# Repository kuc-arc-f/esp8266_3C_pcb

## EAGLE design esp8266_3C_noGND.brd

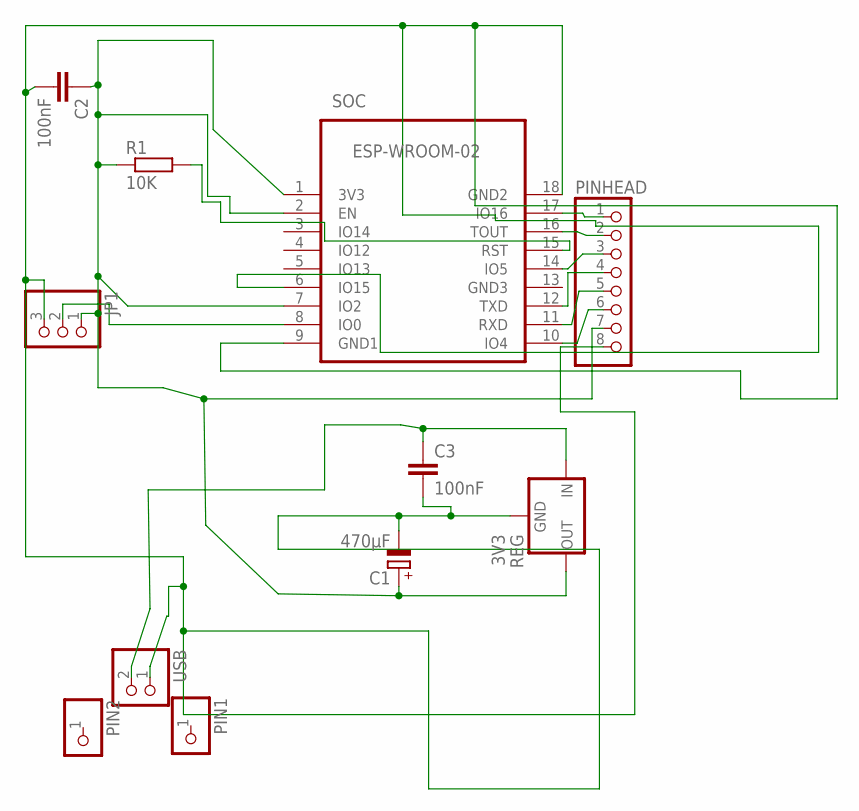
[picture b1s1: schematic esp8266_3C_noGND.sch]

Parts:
C1: 470μF; E2,5-7
C2, C3: 100nF; C0603
JP1: PINHD-1X3; 1X03
PIN1, PIN2: PINHD-1X1; 1X01
PINHEAD: PINHD-1X8; 1X08
R1: 10K; R0603
REG: 3V3; 78XXS
SOC: ESP-WROOM-02; FRONT-FACE-CP2
USB: PINHD-1X2; 1X02

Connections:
unnamed: JP1.2, SOC.8 (IO0)
unnamed: C3.1, REG.IN, USB.2
unnamed: PINHEAD.1, SOC.17 (IO16)
unnamed: PINHEAD.2, SOC.16 (TOUT)
unnamed: PINHEAD.3, SOC.14 (IO5)
unnamed: PINHEAD.4, SOC.12 (TXD)
unnamed: PINHEAD.5, SOC.11 (RXD)
unnamed: PINHEAD.6, SOC.10 (IO4)
unnamed: C1.+, C2.1, JP1.1, PINHEAD.7, R1.1, REG.OUT, SOC.1 (3V3), SOC.2 (EN), SOC.7 (IO2)
unnamed: R1.2, SOC.15 (RST)
USB: C1.-, C2.2, C3.2, JP1.3, PINHEAD.8, REG.GND, SOC.6 (IO15), SOC.9 (GND1), SOC.18 (GND2), USB.1

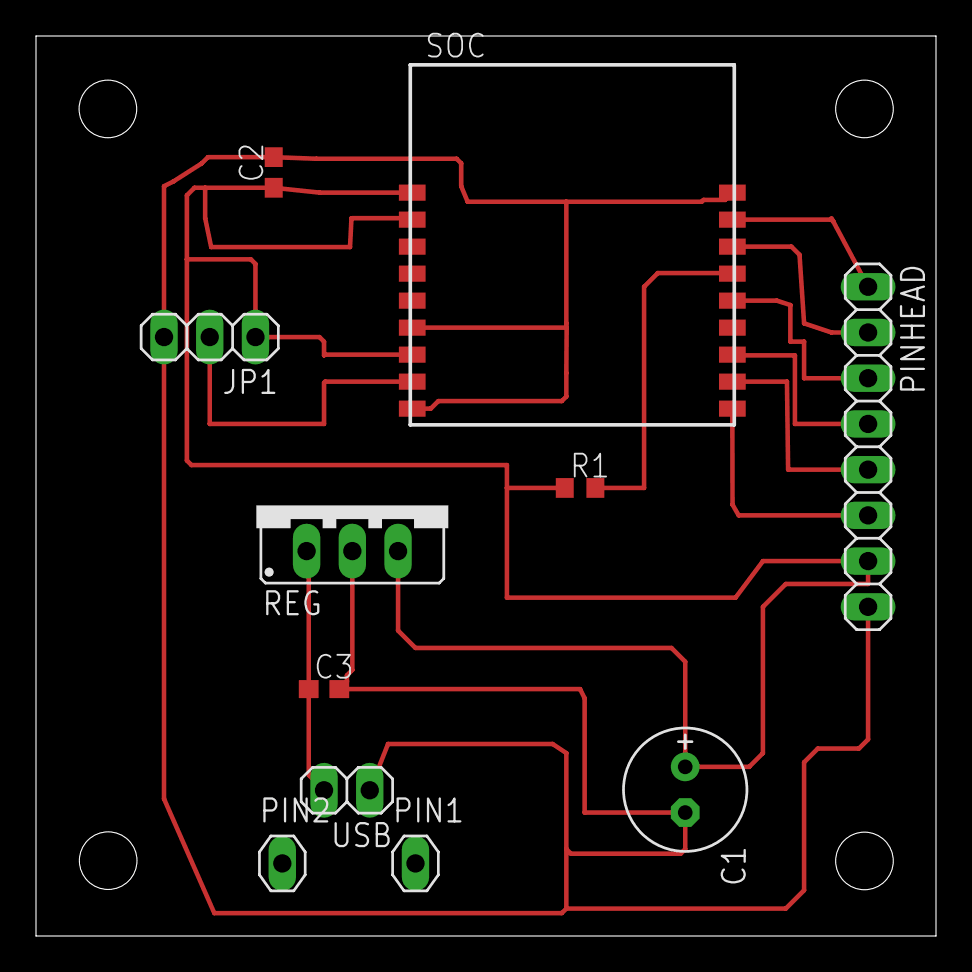
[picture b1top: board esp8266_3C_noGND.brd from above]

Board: 2 copper layers, 50.0 x 50.0 mm, 11 parts (0 on the bottom side), 11 nets.

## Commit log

2016-06-07 new, 06-07A1
